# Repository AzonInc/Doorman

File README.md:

<div align="justify">

  **Doorman S3** is a versatile intercom gateway designed to connect your [TCS](https://www.tcsag.de/) or [Koch](https://www.kochag.ch/) intercom system to any home automation platform. It's also compatible with rebranded versions of [Niko](https://www.niko.eu/), [Scantron](https://scantron.dk/), and older [Jung](https://www.jung-group.com/) TKM intercom models.

  But that's not all - the **Doorman S3** is more than just an intercom bridge. With its integrated relay, you can simulate button presses to control door openers or lights, supporting up to **40V** and a maximum of **2.5A**. 

  Even if your intercom system isn't directly listed, if it operates on a **2-wire bus** in the **14-24V DC range**, you may still be able to implement other protocols. Additionally, you can monitor voltage levels from older intercom systems to trigger actions based on those readings.

  For more information on the manufacturing process, head to the **Manufacturing** section further down.

</div>

<div align="justify">

  Before diving into the installation process, visit the [Doorman Docs](https://doorman.azon.ai/) for comprehensive setup guides.

  Doorman consists of **both hardware and firmware**, so the documentation covers everything you need to get the system up and running — from preparing and assembling the hardware components to flashing and configuring the firmware. You'll find step-by-step instructions for connecting the device, installing the firmware, configuring networking and access settings, and verifying that everything is working correctly.

  If you're setting up Doorman for the first time, the **Getting Started** section is the best place to begin. The docs also include troubleshooting tips, configuration examples, and guidance for updating or customizing the firmware.

  If you have questions, run into issues, or want to discuss ideas or improvements, don't hesitate to reach out on [Discord](https://discord.gg/t2d34dvmBf) or open a discussion on [GitHub Issues](https://github.com/azoninc/doorman/issues). I'm happy to help, and the community is always welcome to share feedback, report bugs, or contribute improvements.

</div>

<div align="justify">

  As part of this open-source, community-driven project, I occasionally make fully assembled Doorman S3 hardware available with the [Doorman Firmware](https://doorman.azon.ai/guide/firmware/installation) pre-installed — ready for seamless integration with Home Assistant.

  This is **not an official, commercial or certified product**. Both the hardware and firmware are outcomes of reverse-engineering work and are offered without any **warranties concerning safety, reliability, or compatibility**.

  **Each device acquired through me directly contributes to the continued development and improvement of the Doorman project.**

  Availability is limited and occurs **without a fixed schedule**. For inquiries, please use [this page](https://doorman.azon.ai/order).

</div>

<div align="justify">

  Check out the [TC:BUS ESPHome component documentation](https://doorman.azon.ai/reference/esphome-component) for detailed instructions on integrating your DIY hardware with the TC:BUS. Whether you're expanding your **Doorman project** or using it as a starting point for your own system, this resource will guide you through seamless integration.

</div>

- **ESP32-S3 Powered** for robust performance
- **USB-C port** for effortless flashing (because USB-C is just cool 😎)
- **Compact design** fits into any setup
- **Configurable WS2812B/SK6812B RGB LED** for event-based visual indicators
- **Two additional GPIOs** for easy expansion (e.g., I²C sensors, external button)
- **Solid-state relay** for switching up to 40V (max. 2.5A)—perfect for older intercom systems
- **Bridge Rectifier** for correcting polarity on bus-wire input
- **TC:BUS Communication** for door functions and detecting the doorbell
- **SIEDLE:IN-HOME-BUS Communication** for door functions and detecting the doorbell
- **Nuki Bridge functionality** with the [Nuki Bridge Addon](https://doorman.azon.ai/guide/firmware/nuki-bridge)

<div align="justify">

  If your TCS or Koch intercom uses **screw terminals labeled `a`, `b`, and `P`** and operates on **24V DC**, it's most likely compatible with **Doorman**.

  For more in-depth compatibility information, refer to the [Compatibility Docs](https://doorman.azon.ai/guide/hardware-compatibility).

</div>

<div align="center">
  
</div>
<br><br>
<div align="justify">

  The repository contains all the files required to produce the core board, including PCB design files, schematics, and the bill of materials (BOM). These resources enable manufacturers or developers to fabricate the board, source the necessary components, and assemble the device according to the reference design.

  You can find all the necessary files for manufacturing the **Doorman Core Board** [here](https://github.com/azoninc/doorman/tree/master/hardware/core_board).

  From my experience working with [PCBWay](https://www.pcbway.com/project/shareproject/Doorman_S3_5bdfd0fb.html), the manufacturing process was smooth and the quality exceeded expectations—especially the clean finish and vibrant PCB colors. Component sourcing was straightforward, and they even included two extra unpopulated PCBs. I soldered the ESP32 modules myself using a heating plate, since I already had modules available at home.

  Communication throughout the process was excellent. Whenever questions came up, they were addressed quickly and professionally. A special thanks goes to Liam and Lynne for their continuous support and patience, even as I made multiple changes along the way. It was genuinely a pleasure working with them.

  If you're looking for a reliable, high-quality one-stop manufacturer, I can definitely recommend [PCBWay](https://www.pcbway.com/project/shareproject/Doorman_S3_5bdfd0fb.html).

</div>

<div align="justify">

  Contributions to the Doorman project are always welcome! Whether it's code improvements, bug fixes, or documentation updates, your help is greatly appreciated. To get started, check out our [Contributing Guidelines](CONTRIBUTING.md).

  Thanks for contributing! 🚀

</div>

<div align="justify">

  The **Doorman S3** project heavily relies on contributions from several key sources. Without their efforts, this project wouldn't be where it is today. ❤️

  **[TCSIntercomArduino](https://github.com/atc1441/TCSintercomArduino)**\
  Different Methods to read from and write to the TCS Bus.\
  Feel free to watch the [Reverse Engineering Video](https://www.youtube.com/watch?v=xFLoauqj9yA) if you're interested.

  **[tcs-monitor](https://github.com/Syralist/tcs-monitor)**\
  An mqtt monitor for listening to the TCS Bus.\
  You can find more information in this [Blog Post](https://blog.syralist.de/posts/smarthome/klingel/).

  **[Doorman](https://github.com/peteh/doorman)**\
  A lot of this Doorman project is based on peteh's one.\
  The main goal is to provide a proper PCB for his Doorman Project.

  **[ESPHome_nuki_lock](https://github.com/uriyacovy/ESPHome_nuki_lock)**\
  This module builds an ESPHome lock platform for Nuki Smartlock (nuki_lock).

  **[AStrehlau](https://github.com/AStrehlau)**\
  Thank you so much for your time, patience, expertise, and every piece of invaluable advice that helped make this project better, smaller, and more affordable.

  **[calibanorg](https://github.com/calibanorg)**\
  Thank you so much for your support, both in terms of encouragement and financial assistance, in the development of Doorman.

  **[mikrocontroller.net](http://mikrocontroller.net/topic/308271)**\
  Thanks to the folks at mikrocontroller.net for figuring out the Siedle In-Home-Bus.

</div>

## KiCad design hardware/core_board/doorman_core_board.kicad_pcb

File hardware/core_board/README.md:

# Core Board KiCad Files

This directory contains all the related Core Board files.
You can also find an interactive BOM [here](https://github.com/azoninc/doorman/tree/master/hardware/core_board/bom).

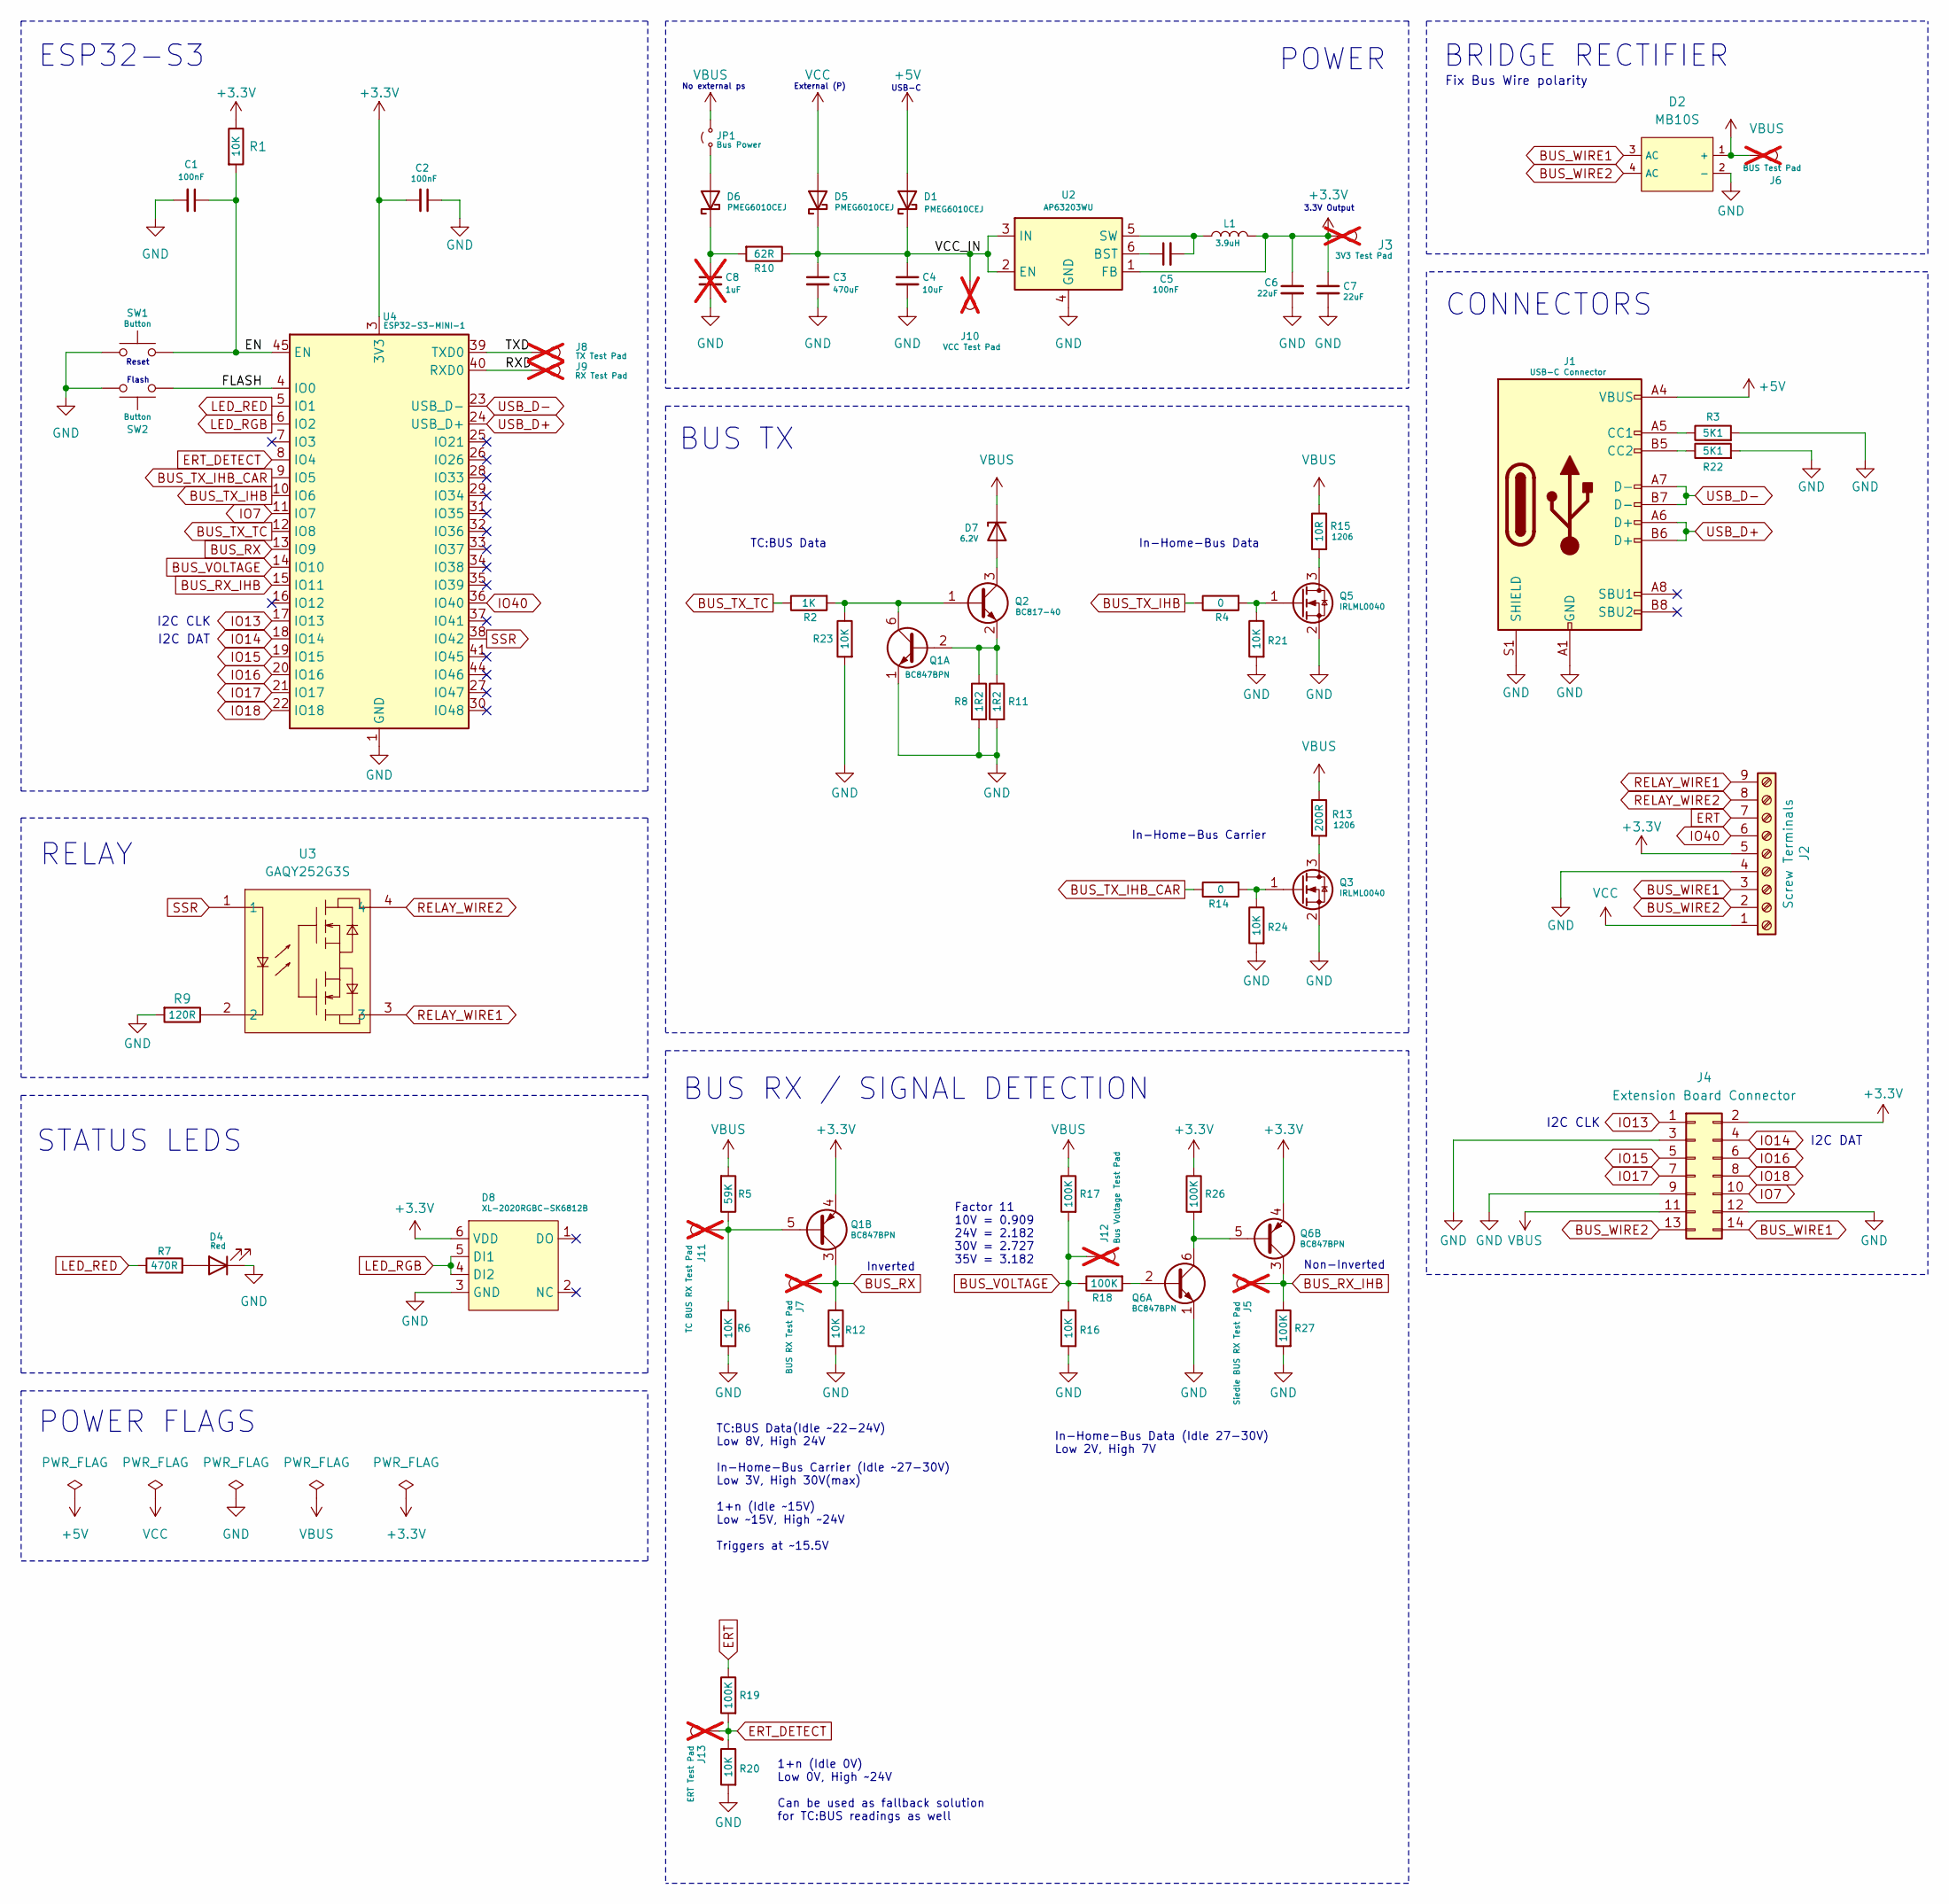
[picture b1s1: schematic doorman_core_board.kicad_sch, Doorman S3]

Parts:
C1, C2, C5: 100nF; C_0603_1608Metric; MPN CC0603KRX7R9BB104; LCSC C14663
C3: 470uF; CP_Elec_8x10; MPN 189RV0027; LCSC C7471889
C4: 10uF; C_1206_3216Metric; MPN CL31B106KBHNNNE; LCSC C89632
C6, C7: 22uF; C_0603_1608Metric; MPN CL10A226MQ8NRNC; LCSC C59461
C8: 1uF; C_1206_3216Metric; MPN CL31B105KBHNNNE; LCSC C1848; not fitted
D1, D5, D6: PMEG6010CEJ; D_SOD-323; MPN PMEG6010CEJ; LCSC C27636122
D2: MB10S; TO-269AA; Reverse Voltage (Vr) 1kV; Forward Voltage (Vf@If) 1.1V@400mA; Part MB10S-50MIL; LCSC C2488
D4: Red; LED_0603_1608Metric; MPN KT-0603R; LCSC C2286
D7: 6.2V; D_MELF; MPN DL4735A; LCSC C841111
D8: XL-2020RGBC-SK6812B; LED-SMD_6P-L2.0-W2.0_XL-2020RGBC; MPN XL-2020RGBC-SK6812B; LCSC C5349956
J1: USB-C Connector; USB_C_Receptacle_HRO_TYPE-C-31-M-12; MPN TYPE-C-31-M-12; LCSC C165948
J2: Screw Terminals; CONN-TH_9P-P2.54_KF128-2.54-9P; MPN DB125-2.54-9P-GN-S; LCSC C918127
J3: 3V3 Test Pad; TestPoint_Pad_D1.0mm; not fitted
J4: Extension Board Connector; PinSocket_2x07_P2.00mm_Vertical_SMD; MPN HC-PM200-4.3H-2x7PS; LCSC C22373875
J5: Siedle BUS RX Test Pad; TestPoint_Pad_D1.0mm; not fitted
J6: BUS Test Pad; TestPoint_Pad_D1.0mm; not fitted
J7: BUS RX Test Pad; TestPoint_Pad_D1.0mm; not fitted
J8: TX Test Pad; TestPoint_Pad_D1.0mm; not fitted
J9: RX Test Pad; TestPoint_Pad_D1.0mm; not fitted
J10: VCC Test Pad; TestPoint_Pad_D1.0mm; not fitted
J11: TC BUS RX Test Pad; TestPoint_Pad_D1.0mm; not fitted
J12: Bus Voltage Test Pad; TestPoint_Pad_D1.0mm; not fitted
J13: ERT Test Pad; TestPoint_Pad_D1.0mm; not fitted
JP1: Bus Power; PinHeader_1x02_P1.27mm_Vertical; MPN DZ127R-11-02-25; LCSC C2935942
L1: 3.9uH; L_Abracon_ASPI-4030S; MPN ANR4030T3R9M; LCSC C6808101
Q1, Q6: BC847BPN; SOT-363_SC-70-6; MPN BC847BPN,115; LCSC C8655
Q2: BC817-40; SOT-23; MPN BC817-40,215; LCSC C52801
Q3, Q5: IRLML0040; SOT-23; MPN IRLML0040; LCSC C5364305
R1, R6, R12, R16, R20, R21, R23, R24: 10K; R_0603_1608Metric; MPN 0603WAF1002T5E; LCSC C25804
R2: 1K; R_0402_1005Metric; MPN 0402WGF1001TCE; LCSC C11702
R3, R22: 5K1; R_0402_1005Metric; MPN 0402WGF5101TCE; LCSC C25905
R4, R14: 0; R_0402_1005Metric; MPN 0402WGF0000TCE; LCSC C17168
R5: 59K; R_0603_1608Metric; MPN 0603WAF5902T5E; LCSC C23085
R7: 470R; R_0603_1608Metric; MPN 0603WAF4700T5E; LCSC C23179
R8, R11: 1R2; R_0805_2012Metric; MPN 0805W8F120KT5E; LCSC C17381
R9: 120R; R_0402_1005Metric; MPN 0402WGF1200TCE; LCSC C25079
R10: 62R; R_1206_3216Metric; MPN AC1206FR-7W62RL; LCSC C5576393
R13: 200R; R_1206_3216Metric; MPN HP06W2F2000T5E; LCSC C2765758
R15: 10R; R_1206_3216Metric; MPN SR1206FR-7T10RL; LCSC C873921
R17, R18, R19, R26, R27: 100K; R_0603_1608Metric; MPN 0603WAF1003T5E; LCSC C25803
SW1, SW2: Button; SW_SPST_B3U-1000P-B; MPN HX-B3U-1000P-1.6N; LCSC C49234121
U2: AP63203WU; TSOT-23-6; MPN AP63203WU-7; LCSC C780769
U3: GAQY252G3S; SOP-4_L4.4-W4.0-P2.54-LS7.0-TL; MPN GAQY252G3S; LCSC C7435106
U4: ESP32-S3-MINI-1; MPN ESP32-S3-MINI-1-N4R2; LCSC C3013941

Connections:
+3.3V: C2.2, C6.1, C7.1, D8.6 (VDD), J2.5, J3.1, J4.2, L1.2, Q1.4 (E2), Q6.4 (E2), R1.1, R26.1, U2.1 (FB), U4.3 (3V3)
+5V: D1.2 (A), J1.A4 (VBUS), J1.A9 (VBUS), J1.B4 (VBUS), J1.B9 (VBUS)
/EN: C1.1, R1.2, SW1.1, U4.45 (EN)
/FLASH: SW2.1, U4.4 (IO0)
/RXD: J9.1, U4.40 (RXD0)
/TXD: J8.1, U4.39 (TXD0)
/VCC_IN: C3.1, C4.1, D1.1 (K), D5.1 (K), J10.1, R10.1, U2.2 (EN), U2.3 (IN)
BUS_RX: J7.1, Q1.3 (C2), R12.1, U4.13 (IO9)
BUS_RX_IHB: J5.1, Q6.3 (C2), R27.1, U4.15 (IO11)
BUS_TX_IHB: R4.1, U4.10 (IO6)
BUS_TX_IHB_CAR: R14.1, U4.9 (IO5)
BUS_TX_TC: R2.1, U4.12 (IO8)
BUS_VOLTAGE: J12.1, R16.1, R17.2, R18.1, U4.14 (IO10)
BUS_WIRE1: D2.3 (AC), J2.3, J4.14
BUS_WIRE2: D2.4 (AC), J2.2, J4.13
ERT: J2.7, R19.1
ERT_DETECT: J13.1, R19.2, R20.1, U4.8 (IO4)
GND: C1.2, C2.1, C3.2, C4.2, C6.2, C7.2, C8.2, D2.2 (-), D4.1 (K), D8.3 (GND), J1.A1 (GND), J1.A12 (GND), J1.B1 (GND), J1.B12 (GND), J1.S1 (SHIELD), J2.4, J4.3, J4.9, J4.12, Q1.1 (E1), Q3.2 (S), Q5.2 (S), Q6.1 (E1), R3.2, R6.2, R8.2, R9.2, R11.2, R12.2, R16.2, R20.2, R21.2, R22.2, R23.2, R24.2, R27.2, SW1.2, SW2.2, U2.4 (GND), U4.1 (GND), U4.2 (GND), U4.42 (GND), U4.43 (GND), U4.46 (GND), U4.47 (GND), U4.48 (GND), U4.49 (GND), U4.50 (GND), U4.51 (GND), U4.52 (GND), U4.53 (GND), U4.54 (GND), U4.55 (GND), U4.56 (GND), U4.57 (GND), U4.58 (GND), U4.59 (GND), U4.60 (GND), U4.61 (GND), U4.62 (GND), U4.63 (GND), U4.64 (GND), U4.65 (GND)
IO7: J4.10, U4.11 (IO7)
IO13: J4.1, U4.17 (IO13)
IO14: J4.4, U4.18 (IO14)
IO15: J4.5, U4.19 (IO15)
IO16: J4.6, U4.20 (IO16)
IO17: J4.7, U4.21 (IO17)
IO18: J4.8, U4.22 (IO18)
IO40: J2.6, U4.36 (IO40)
LED_RED: R7.1, U4.5 (IO1)
LED_RGB: D8.4 (DI2), D8.5 (DI1), U4.6 (IO2)
unnamed: D4.2 (A), R7.2
unnamed: D6.2 (A), JP1.1 (A)
unnamed: C8.1, D6.1 (K), R10.2
unnamed: D7.2 (A), Q2.3 (C)
unnamed: J1.A5 (CC1), R22.1
unnamed: J1.B5 (CC2), R3.1
unnamed: Q1.2 (B1), Q2.2 (E), R8.1, R11.1
unnamed: Q1.6 (C1), Q2.1 (B), R2.2, R23.1
unnamed: J11.1, Q1.5 (B2), R5.1, R6.1
unnamed: Q3.3 (D), R13.2
unnamed: Q3.1 (G), R14.2, R24.1
unnamed: Q5.3 (D), R15.2
unnamed: Q5.1 (G), R4.2, R21.1
unnamed: Q6.2 (B1), R18.2
unnamed: Q6.5 (B2), Q6.6 (C1), R26.2
unnamed: R9.1, U3.2
unnamed: C5.1, U2.6 (BST)
unnamed: C5.2, L1.1, U2.5 (SW)
RELAY_WIRE1: J2.9, U3.3
RELAY_WIRE2: J2.8, U3.4
SSR: U3.1, U4.38 (IO42)
USB_D+: J1.A6 (D+), J1.B6 (D+), U4.24 (USB_D+)
USB_D-: J1.A7 (D-), J1.B7 (D-), U4.23 (USB_D-)
VBUS: D2.1 (+), D7.1 (K), J4.11, J6.1, JP1.2 (B), R5.2, R13.1, R15.1, R17.1
VCC: D5.2 (A), J2.1

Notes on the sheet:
In-Home-Bus Data (Idle 27-30V) Low 2V, High 7V
In-Home-Bus Carrier
I2C CLK
USB-C
TC:BUS Data(Idle ~22-24V) Low 8V, High 24V In-Home-Bus Carrier (Idle ~27-30V) Low 3V, High 30V(max) 1+n (Idle ~15V) Low ~15V, High ~24V Triggers at ~15.5V
No external ps
POWER
In-Home-Bus Data
I2C DAT
CONNECTORS
3.3V Output
TC:BUS Data
STATUS LEDS
External (P)
Flash
ESP32-S3
Fix Bus Wire polarity
Reset
BUS RX / SIGNAL DETECTION
RELAY
Factor 11 10V = 0.909 24V = 2.182 30V = 2.727 35V = 3.182
BRIDGE RECTIFIER
1+n (Idle 0V) Low 0V, High ~24V Can be used as fallback solution for TC:BUS readings as well
POWER FLAGS
Inverted
Non-Inverted
BUS TX

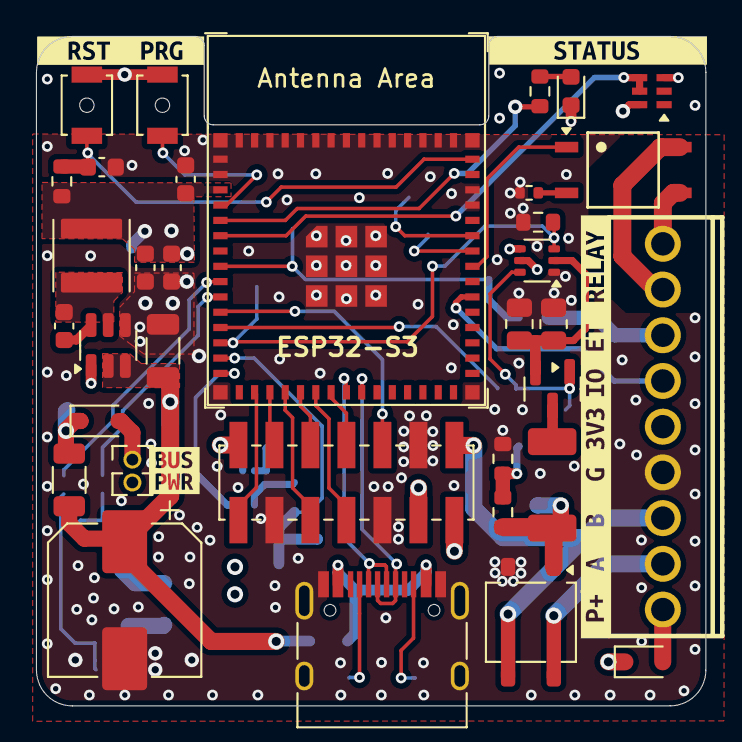
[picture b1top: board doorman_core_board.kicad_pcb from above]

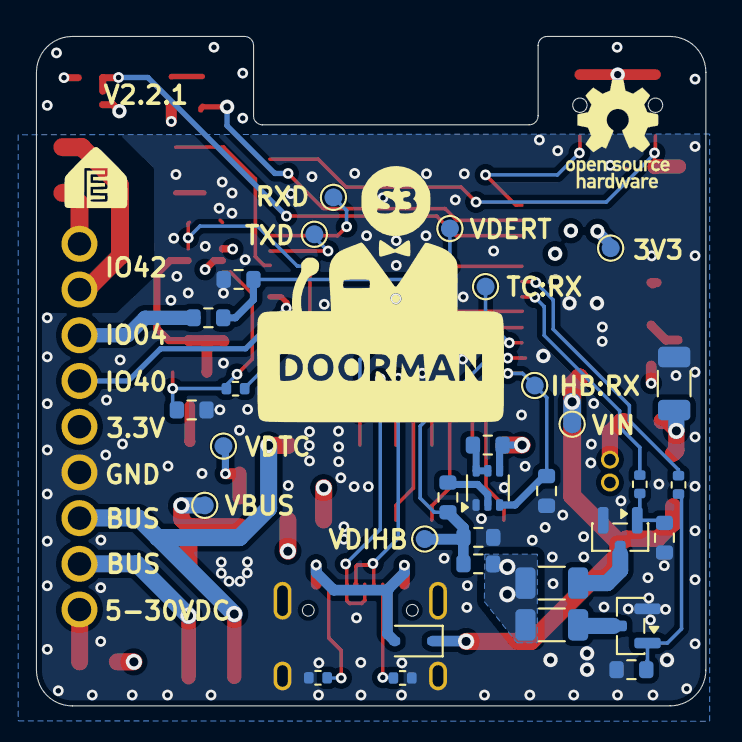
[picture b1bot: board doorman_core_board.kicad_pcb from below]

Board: 4 copper layers, 37.2 x 37.2 mm, 76 parts (32 on the bottom side), 53 nets.

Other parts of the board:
kibuzzard-69BAB7C5: G***; kibuzzard-69BAB7C5
kibuzzard-69BAB57C: G***; kibuzzard-69BAB57C
kibuzzard-69BAB542: G***; kibuzzard-69BAB542
kibuzzard-69BABEC4: G***; kibuzzard-69BABEC4
kibuzzard-69BACA52: G***; kibuzzard-69BACA52
kibuzzard-69BACA90: G***; kibuzzard-69BACA90
kibuzzard-69BACB1F: G***; kibuzzard-69BACB1F
kibuzzard-69BACB5F: G***; kibuzzard-69BACB5F
kibuzzard-69BD6C3C: G***; kibuzzard-69BD6C3C
kibuzzard-69BD6F46: G***; kibuzzard-69BD6F46

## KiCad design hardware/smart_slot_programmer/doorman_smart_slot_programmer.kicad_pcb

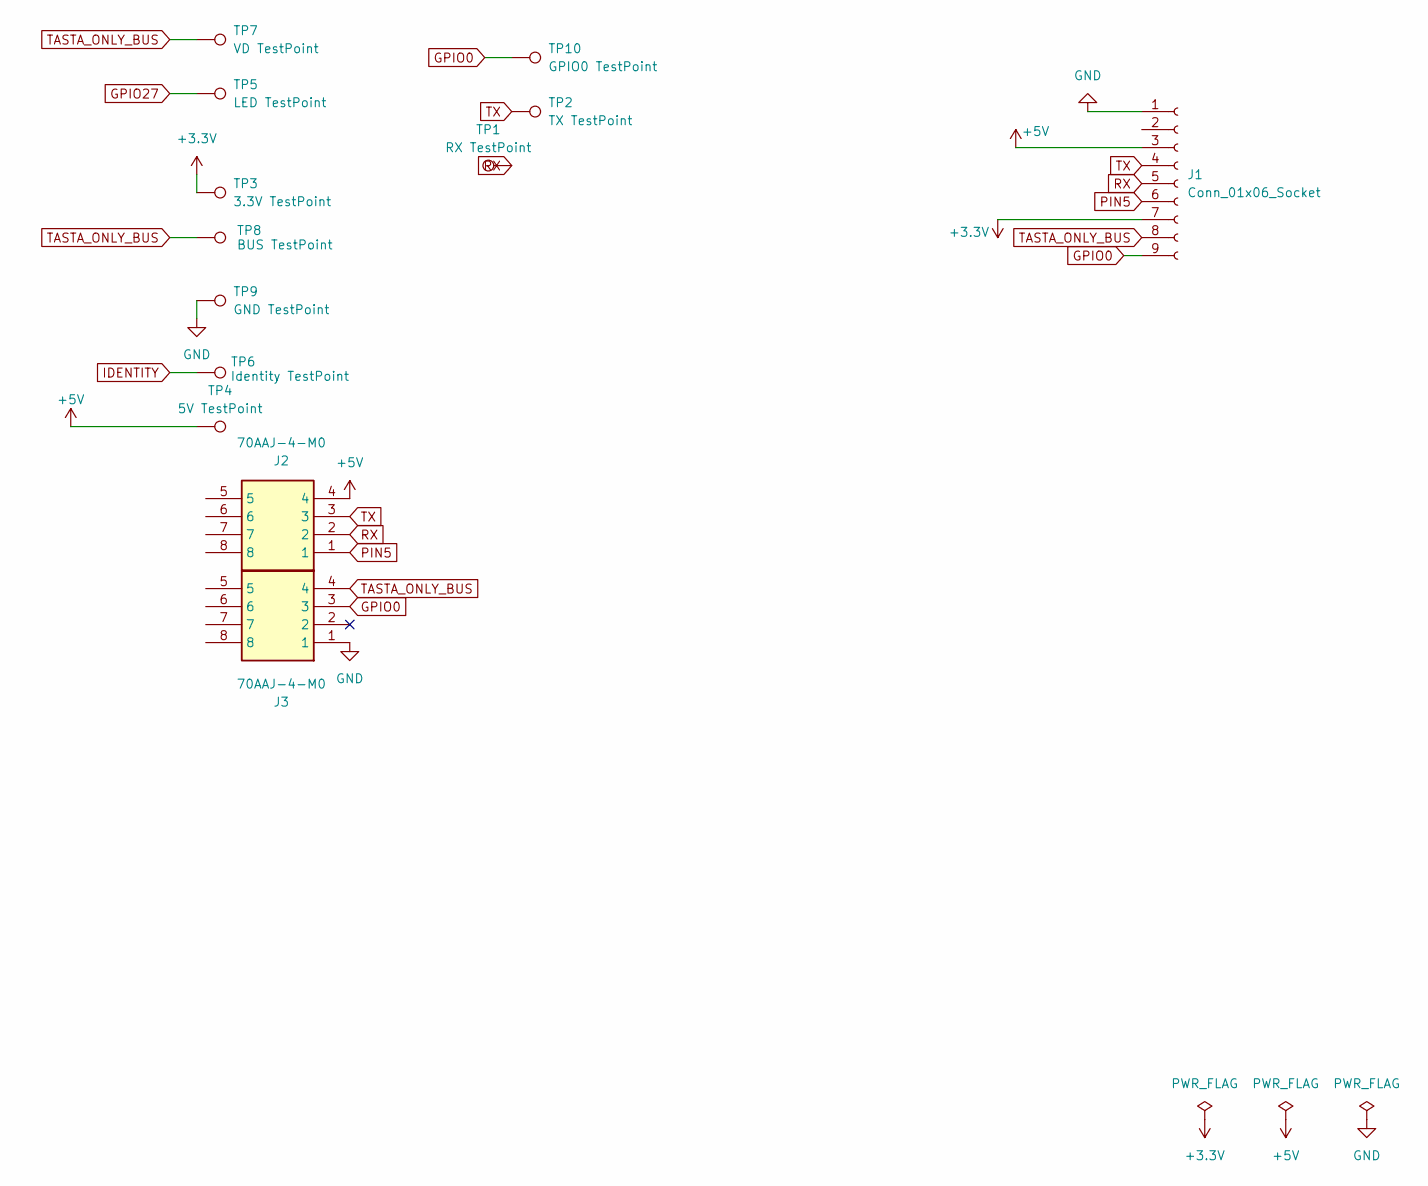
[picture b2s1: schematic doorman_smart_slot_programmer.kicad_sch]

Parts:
J1: Conn_01x06_Socket; PinSocket_1x09_P2.54mm_Horizontal
J2, J3: 70AAJ-4-M0; 70AAJ4M0; Manufacturer_Part_Number 70AAJ-4-M0; Mouser Part Number 652-70AAJ-4-M0
TP1: RX TestPoint; TestPoint_Pad_D1.0mm
TP2: TX TestPoint; TestPoint_Pad_D1.0mm
TP3: 3.3V TestPoint; TestPoint_Pad_D1.0mm
TP4: 5V TestPoint; TestPoint_Pad_D1.0mm
TP5: LED TestPoint; TestPoint_Pad_D1.0mm
TP6: Identity TestPoint; TestPoint_Pad_D1.0mm
TP7: VD TestPoint; TestPoint_Pad_D1.0mm
TP8: BUS TestPoint; TestPoint_Pad_D1.0mm
TP9: GND TestPoint; TestPoint_Pad_D1.0mm
TP10: GPIO0 TestPoint; TestPoint_Pad_D1.0mm

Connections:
+3.3V: J1.7, TP3.1
+5V: J1.3, J2.4, TP4.1
GND: J1.1, J3.1, TP9.1
GPIO0: J1.9, J3.3, TP10.1
GPIO27: TP5.1
IDENTITY: TP6.1
PIN5: J1.6, J2.1
RX: J1.5, J2.2, TP1.1
TASTA_ONLY_BUS: J1.8, J3.4, TP7.1, TP8.1
TX: J1.4, J2.3, TP2.1

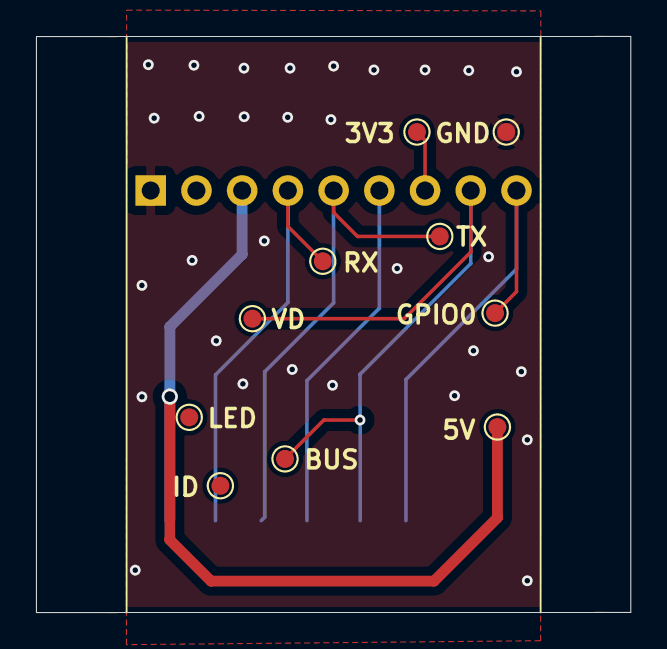
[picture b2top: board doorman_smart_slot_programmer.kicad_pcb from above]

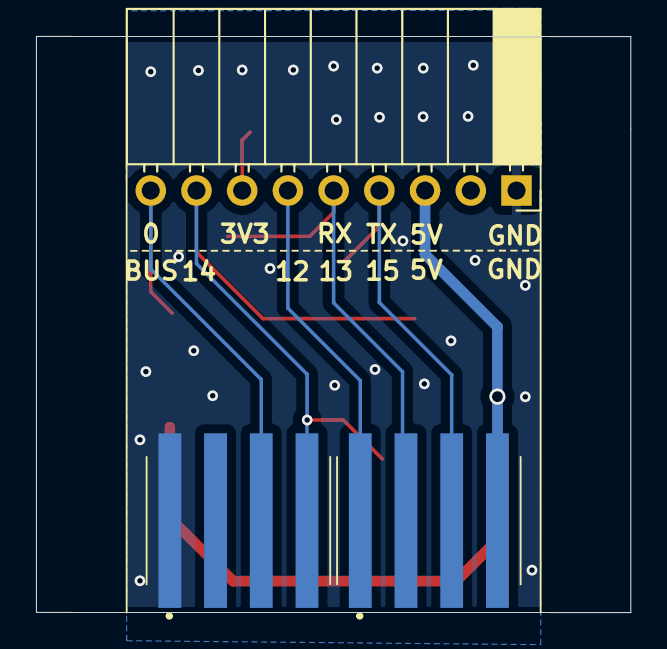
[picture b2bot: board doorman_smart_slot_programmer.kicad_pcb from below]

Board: 4 copper layers, 33.0 x 32.0 mm, 13 parts (3 on the bottom side), 8 nets.

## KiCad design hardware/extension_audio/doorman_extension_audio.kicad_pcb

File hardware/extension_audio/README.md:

# Audio Extension Board KiCad Files

This directory contains all the related Audio Extension Board files.
You can also find an interactive BOM [here](https://github.com/azoninc/doorman/tree/master/hardware/extension_audio/bom).

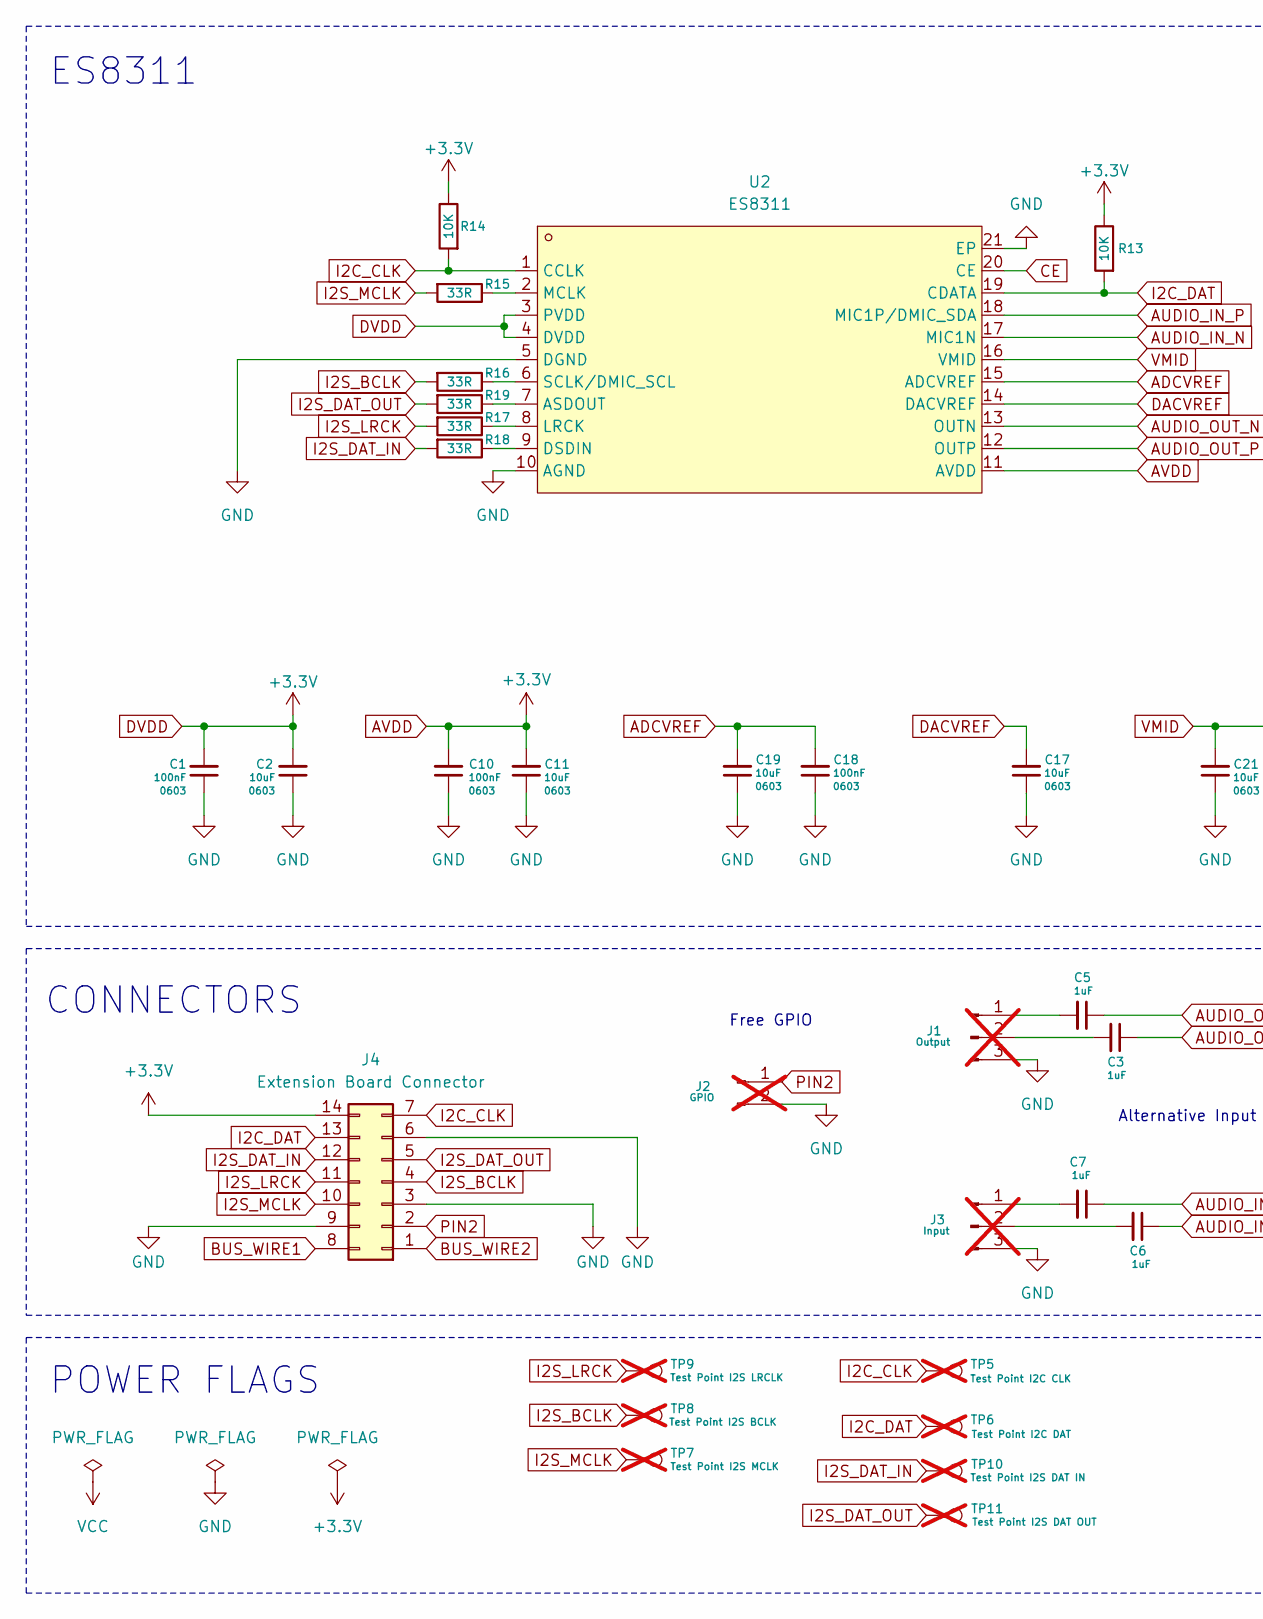
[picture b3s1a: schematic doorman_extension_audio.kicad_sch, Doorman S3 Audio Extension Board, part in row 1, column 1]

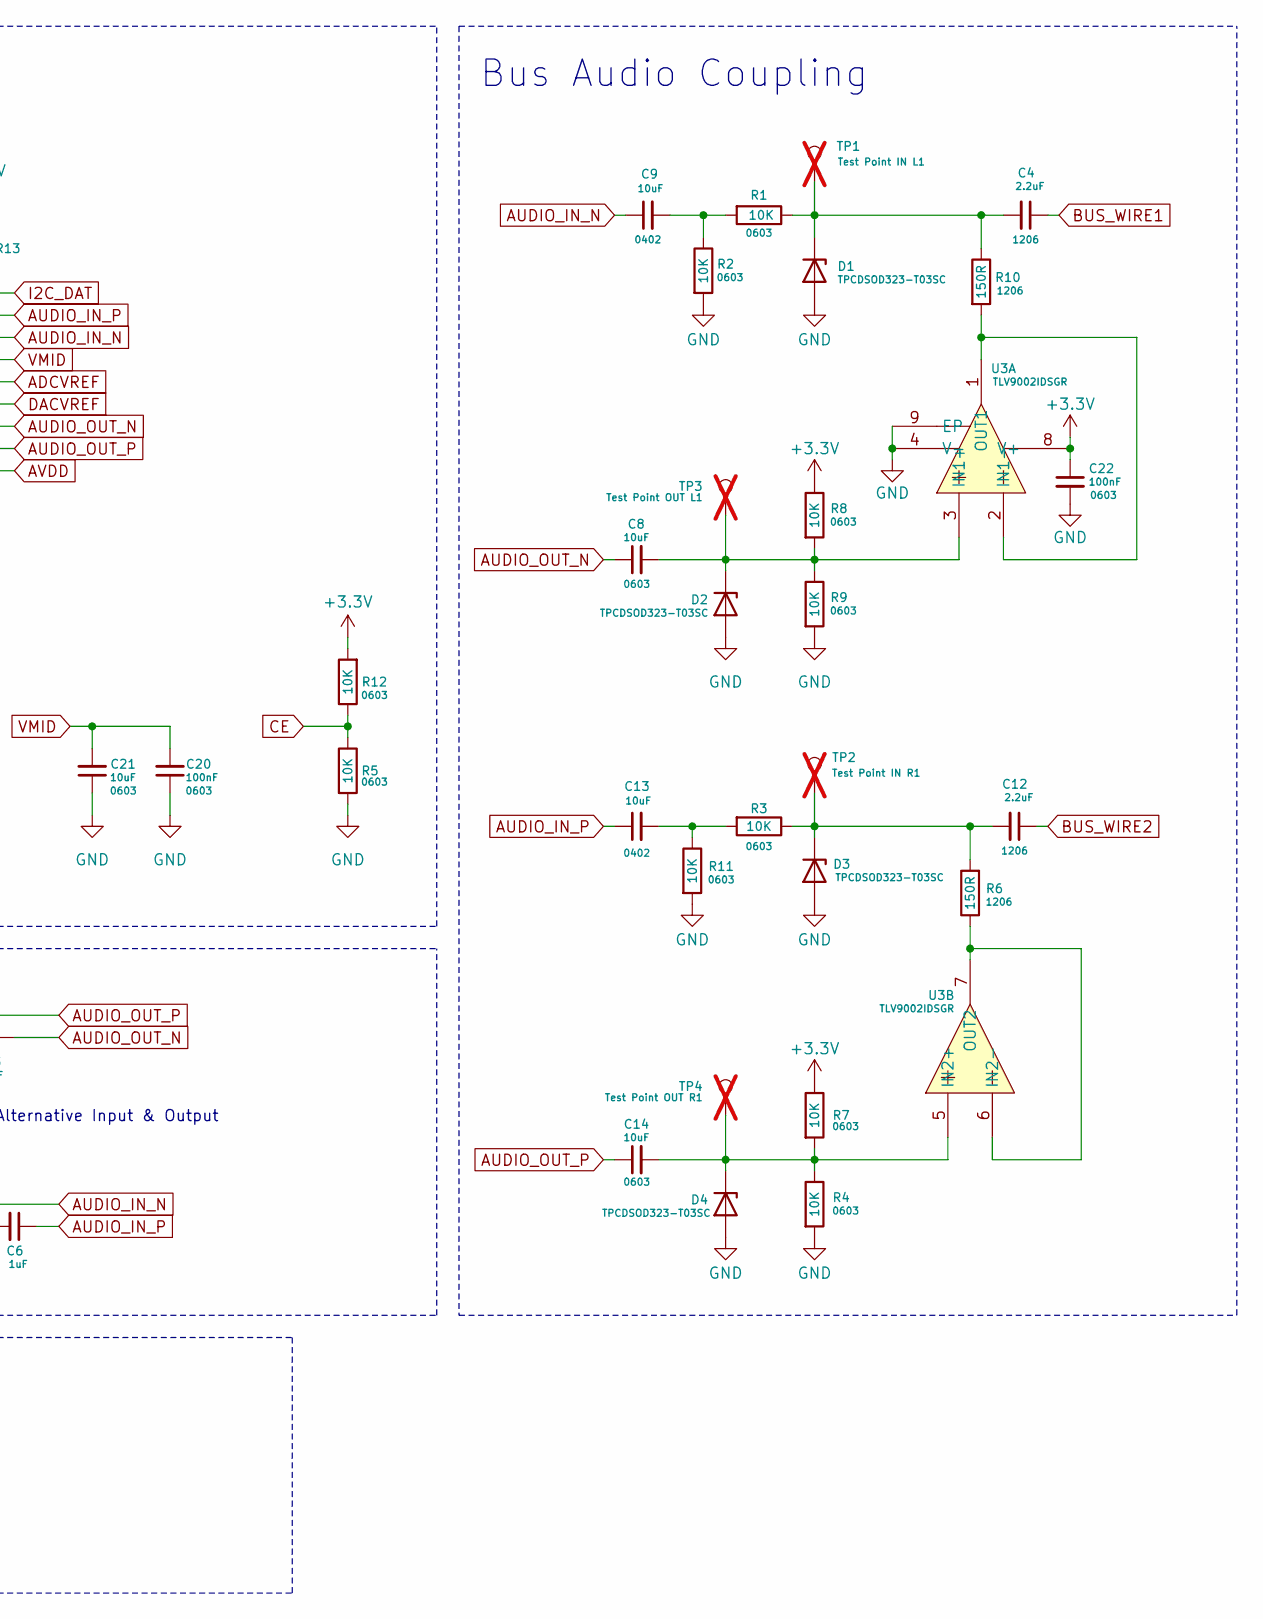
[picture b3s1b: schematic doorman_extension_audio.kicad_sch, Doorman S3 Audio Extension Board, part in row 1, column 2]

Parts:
C1, C10, C18, C20, C22: 100nF; C_0603_1608Metric; MPN CC0603KRX7R9BB104; LCSC C14663
C2, C8, C11, C14, C17, C19, C21: 10uF; C_0603_1608Metric; MPN GRM188Z71A106KA73D; LCSC C2959727
C3, C5, C6, C7: 1uF; C_0603_1608Metric; MPN CL10B105KA8NNNC; LCSC C29936
C4, C12: 2.2uF; C_1206_3216Metric; MPN CL31B225KBHNNNE; LCSC C50254
C9, C13: 10uF; C_0402_1005Metric; MPN CL05A106MQ5NUNC; LCSC C15525
D1, D2, D3, D4: TPCDSOD323-T03SC; D_SOD-323; MPN TPCDSOD323-T03SC; LCSC C907860
J1: Output; PinHeader_1x03_P2.54mm_Vertical; not fitted
J2: GPIO; PinHeader_1x02_P2.54mm_Vertical; not fitted
J3: Input; PinHeader_1x03_P2.54mm_Vertical; not fitted
J4: Extension Board Connector; PinHeader_2x07_P2.00mm_Vertical_SMD; MPN PZ200-2-07-S; LCSC C3294446
R1, R2, R3, R4, R5, R7, R8, R9, R11, R12, R13, R14: 10K; R_0603_1608Metric; MPN 0603WAF1002T5E; LCSC C25804
R6, R10: 150R; R_1206_3216Metric; MPN 1206W4F1500T5E; LCSC C17917
R15, R16, R17, R18, R19: 33R; R_0603_1608Metric; MPN 0603WAF330JT5E; LCSC C23140
TP1: Test Point IN L1; TestPoint_Pad_D1.0mm; not fitted
TP2: Test Point IN R1; TestPoint_Pad_D1.0mm; not fitted
TP3: Test Point OUT L1; TestPoint_Pad_D1.0mm; not fitted
TP4: Test Point OUT R1; TestPoint_Pad_D1.0mm; not fitted
TP5: Test Point I2C CLK; TestPoint_Pad_D1.0mm; not fitted
TP6: Test Point I2C DAT; TestPoint_Pad_D1.0mm; not fitted
TP7: Test Point I2S MCLK; TestPoint_Pad_D1.0mm; not fitted
TP8: Test Point I2S BCLK; TestPoint_Pad_D1.0mm; not fitted
TP9: Test Point I2S LRCLK; TestPoint_Pad_D1.0mm; not fitted
TP10: Test Point I2S DAT IN; TestPoint_Pad_D1.0mm; not fitted
TP11: Test Point I2S DAT OUT; TestPoint_Pad_D1.0mm; not fitted
U2: ES8311; QFN40P300X300X60-21N; MPN ES8311; LCSC Part C962342
U3: TLV9002IDSGR; WSON-8_L2.0-W2.0-P0.65-BL-EP; MPN TLV9002IDSGR; LCSC Part C2876157

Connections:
ADCVREF: C18.2, C19.2, U2.15 (ADCVREF)
AUDIO_IN_N: C7.1, C9.1, U2.17 (MIC1N)
AUDIO_IN_P: C6.1, C13.1, U2.18 (MIC1P/DMIC_SDA)
AUDIO_OUT_N: C3.1, C8.1, U2.13 (OUTN)
AUDIO_OUT_P: C5.1, C14.1, U2.12 (OUTP)
AVDD: C1.2, C2.2, C10.2, C11.2, C22.1, J4.14, R7.1, R8.1, R12.2, R13.1, R14.1, U2.3 (PVDD), U2.4 (DVDD), U2.11 (AVDD), U3.8 (V+)
BUS_WIRE1: C4.1, J4.8
BUS_WIRE2: C12.1, J4.1
CE: R5.1, R12.1, U2.20 (CE)
DACVREF: C17.2, U2.14 (DACVREF)
GND: C1.1, C2.1, C10.1, C11.1, C17.1, C18.1, C19.1, C20.1, C21.1, C22.2, D1.2 (A), D2.2 (A), D3.2 (A), D4.2 (A), J1.3, J2.2, J3.3, J4.3, J4.6, J4.9, R2.2, R4.2, R5.2, R9.2, R11.2, U2.5 (DGND), U2.10 (AGND), U2.21 (EP), U3.4 (V-), U3.9 (EP)
I2C_CLK: J4.7, R14.2, TP5.1, U2.1 (CCLK)
I2C_DAT: J4.13, R13.2, TP6.1, U2.19 (CDATA)
I2S_BCLK: J4.4, R16.2, TP8.1
I2S_DAT_IN: J4.12, R18.2, TP10.1
I2S_DAT_OUT: J4.5, R19.2, TP11.1
I2S_LRCK: J4.11, R17.2, TP9.1
I2S_MCLK: J4.10, R15.2, TP7.1
unnamed: C9.2, R1.2, R2.1
unnamed: C13.2, R3.2, R11.1
unnamed: C4.2, D1.1 (K), R1.1, R10.1, TP1.1
unnamed: C8.2, D2.1 (K), R8.2, R9.1, TP3.1, U3.3 (IN1+)
unnamed: C12.2, D3.1 (K), R3.1, R6.2, TP2.1
unnamed: C14.2, D4.1 (K), R4.1, R7.2, TP4.1, U3.5 (IN2+)
unnamed: C5.2, J1.1
unnamed: C3.2, J1.2
unnamed: C7.2, J3.1
unnamed: C6.2, J3.2
unnamed: R19.1, U2.7 (ASDOUT)
unnamed: R18.1, U2.9 (DSDIN)
unnamed: R17.1, U2.8 (LRCK)
unnamed: R15.1, U2.2 (MCLK)
unnamed: R16.1, U2.6 (SCLK/DMIC_SCL)
unnamed: R10.2, U3.1 (OUT1), U3.2 (IN1-)
unnamed: R6.1, U3.6 (IN2-), U3.7 (OUT2)
PIN2: J2.1, J4.2
VMID: C20.2, C21.2, U2.16 (VMID)

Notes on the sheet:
ES8311
Bus Audio Coupling
CONNECTORS
Free GPIO
Alternative Input & Output
POWER FLAGS

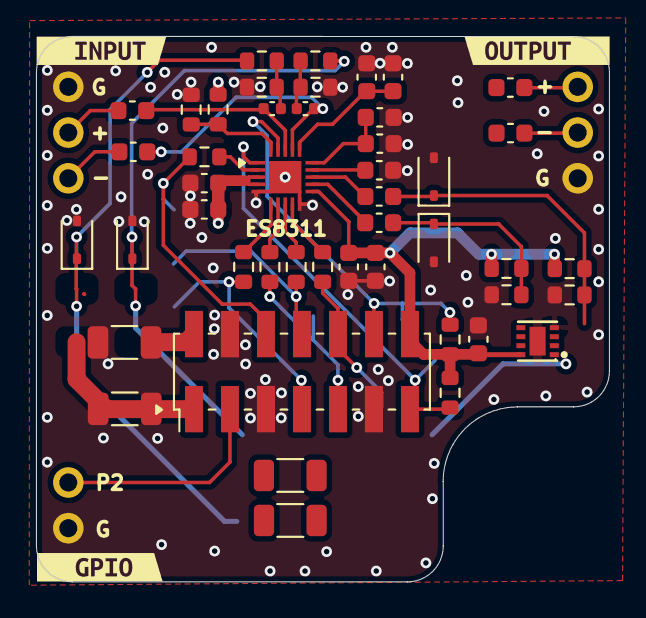
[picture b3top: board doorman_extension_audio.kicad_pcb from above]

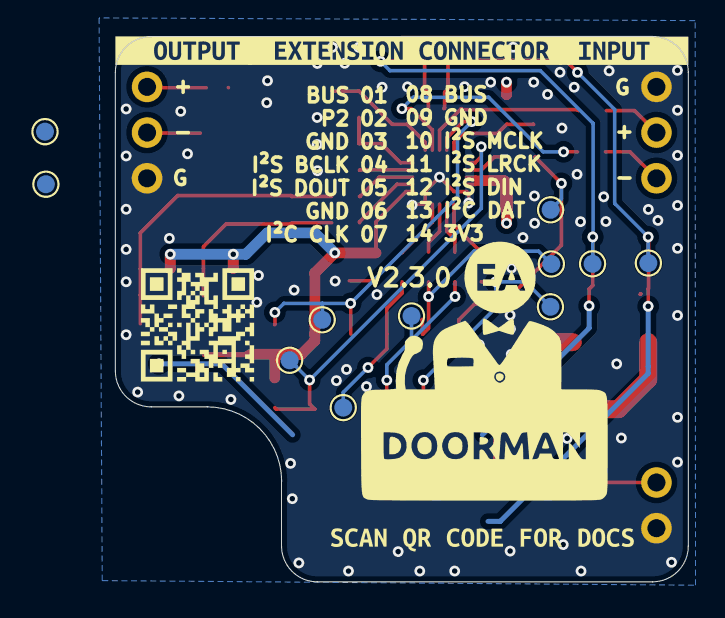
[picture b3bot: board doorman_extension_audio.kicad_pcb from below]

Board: 4 copper layers, 31.8 x 30.3 mm, 67 parts (15 on the bottom side), 37 nets.

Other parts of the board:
kibuzzard-69BBCF9C: G***; kibuzzard-69BBCF9C
kibuzzard-69BBD00D: G***; kibuzzard-69BBD00D
kibuzzard-69BBD0F2: G***; kibuzzard-69BBD0F2
kibuzzard-69BBD4A4: G***; kibuzzard-69BBD4A4
kibuzzard-69BBD107: G***; kibuzzard-69BBD107
kibuzzard-69BBEEE6: G***; kibuzzard-69BBEEE6
kibuzzard-69DCDFB0: G***; kibuzzard-69DCDFB0
